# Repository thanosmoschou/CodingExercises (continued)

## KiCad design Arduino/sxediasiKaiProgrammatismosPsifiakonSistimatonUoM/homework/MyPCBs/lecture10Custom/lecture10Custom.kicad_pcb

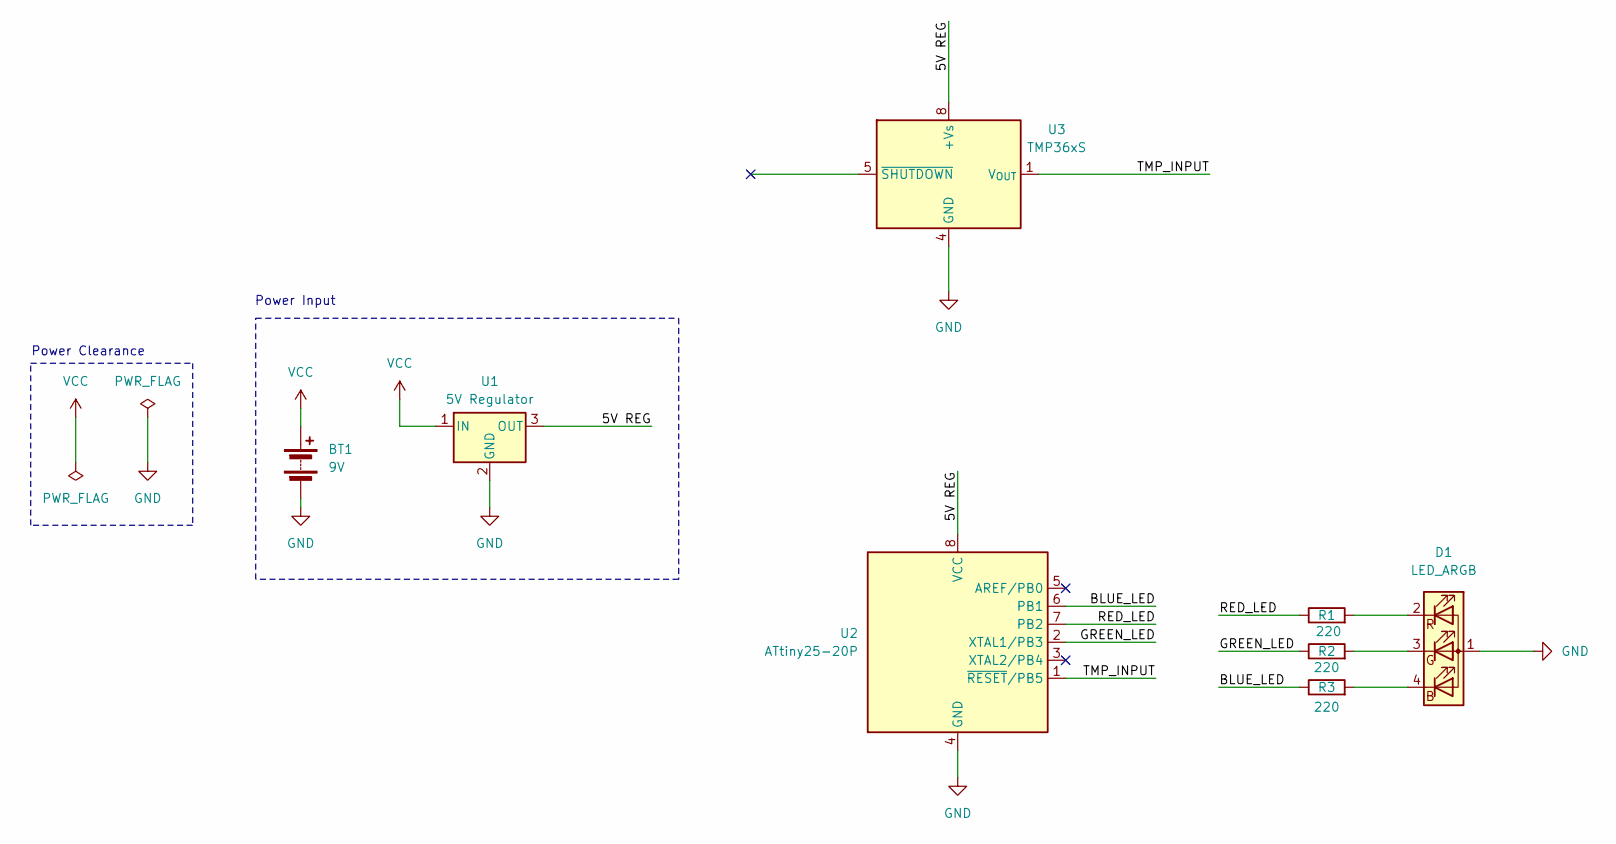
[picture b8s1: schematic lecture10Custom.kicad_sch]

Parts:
BT1: 9V; BatteryHolder_MPD_BA9VPC_1xPP3
D1: LED_ARGB; LED_BL-FL7680RGB
R1, R2, R3: 220; R_Axial_DIN0207_L6.3mm_D2.5mm_P10.16mm_Horizontal
U1: 5V Regulator; TO-220-3_Vertical
U2: ATtiny25-20P; DIP-8_W7.62mm
U3: TMP36xS; SOIC-8_3.9x4.9mm_P1.27mm

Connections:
/5V REG: U1.3 (OUT), U2.8 (VCC), U3.8 (+Vs)
/BLUE_LED: R3.1, U2.6 (PB1)
/GREEN_LED: R2.1, U2.2 (XTAL1/PB3)
/RED_LED: R1.1, U2.7 (PB2)
/TMP_INPUT: U2.1 (~RESET/PB5), U3.1 (V_{OUT})
GND: BT1.2 (-), D1.1 (A), U1.2 (GND), U2.4 (GND), U3.4 (GND)
unnamed: D1.4 (BK), R3.2
unnamed: D1.3 (GK), R2.2
unnamed: D1.2 (RK), R1.2
VCC: BT1.1 (+), U1.1 (IN)

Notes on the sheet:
Power Clearance
Power Input

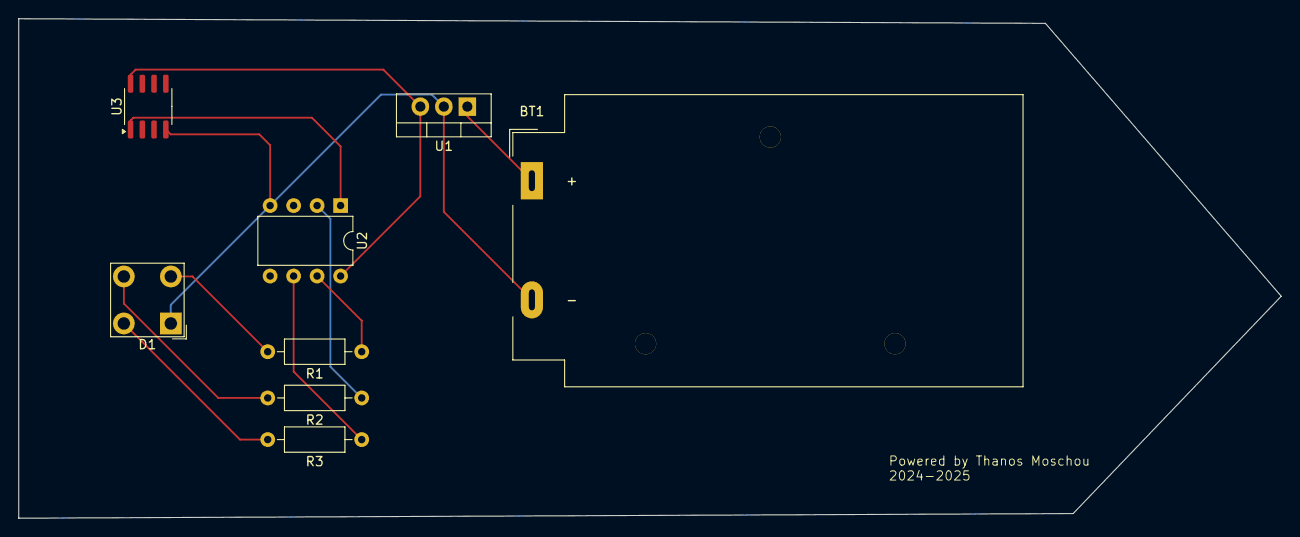
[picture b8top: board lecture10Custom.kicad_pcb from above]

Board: 2 copper layers, 136.5 x 54.0 mm, 8 parts (0 on the bottom side), 10 nets.

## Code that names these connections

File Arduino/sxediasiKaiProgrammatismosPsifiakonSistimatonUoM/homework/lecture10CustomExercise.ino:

/*
Author: Thanos Moschou

Description: A circuit that changes
the LED color depending on temperature.
For temperatures under 0 degrees Celcius
the led color is blue, for temperatures
under 30 degrees Celcius the led is green, 
otherwise it is red.

Components:

1 ATTiny
1 breadboard
1 5V regulator LM7805
1 Temperature Sensor TMP36
1 9V battery
1 RGB Led
3 Resistors 220 Ohm
Jumper wires
*/

int temperPin = A0; // PB5 is also A0
int redPin = 2; // PB2
int bluePin = 1; // PB1
int greenPin = 3; // PB3

void setup()
{
  pinMode(redPin, OUTPUT);
  pinMode(bluePin, OUTPUT);
  pinMode(greenPin, OUTPUT);
  
  digitalWrite(redPin, LOW);
  digitalWrite(bluePin, LOW);
  digitalWrite(greenPin, LOW);
}

void loop()
{
  int d = analogRead(temperPin);
  float temperature = 0.49 * d - 50;
  
  if (temperature < 0) {
    digitalWrite(bluePin, HIGH);
    digitalWrite(redPin, LOW);
    digitalWrite(greenPin, LOW);
  } else if (temperature < 30) {
    digitalWrite(greenPin, HIGH);
    digitalWrite(bluePin, LOW);
    digitalWrite(redPin, LOW);
  } else {
    digitalWrite(redPin, HIGH);
    digitalWrite(bluePin, LOW);
    digitalWrite(greenPin, LOW);
  }
  
  delay(500);
}

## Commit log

2024-06-08 Create LICENSE
2024-06-08 second commit
2024-06-14 add revision android exercise
2024-07-05 add android past exams solutions
2024-07-05 minor changes
2024-07-06 changes to some comments
2024-07-09 mobile development solution september2022
2024-07-16 add july 2024 mobile solution
2024-08-15 add pdc lab solutions
2024-08-16 add lab8
2024-08-16 add lab9
2024-08-17 add lab 10 and lab 11 and made some code format fixes
2024-09-03 modifications
2024-09-09 leetcode changes
2024-09-09 concurrency leetcode problem
2024-09-20 change lab6 of pdc and add Go section
2024-09-21 add exercism exercises
2024-09-22 new exercises
2024-09-23 go exercises
2024-09-23 more go exercises
2024-10-19 complete learning mode in go
2024-10-19 leetcode solution
2024-10-20 more leetcode
2024-10-26 leetcode
2024-10-28 arduino added
2024-10-31 more leetcode75
2024-11-03 arduino practice
2024-11-04 goroutines pdc
2024-11-05 pdc lab3
2024-11-10 arduino exercises
2024-11-11 solidity
2024-11-12 vote
2024-11-12 another solidity example
2024-11-18 add demo for solidity
2024-11-23 more arduino
2024-11-23 minor improvements
2024-12-29 edit
2025-01-29 new revision exercises
2025-01-29 ch4ex3
2025-01-29 new exercises with pcb's
2025-01-29 new custom exerc
2025-01-29 new custom exercise
2025-01-29 edit pcb notes
2025-01-29 notes and new custom exercise
2025-01-29 new custom
2025-01-29 add spring boot section
2025-02-05 edit api
2025-02-07 add spring boot security api exercise
2025-02-11 secure book api v2
2025-02-13 new arduino exercise
2025-02-28 clean structure
2025-03-03 edit spring boot project and create a basic css project of a profile card
2025-03-04 sign up page
2025-03-10 webflux demo
2025-03-10 web flux demo
2025-03-11 video streaming demo
2025-03-20 spring boot demo
2025-03-20 more
2025-05-03 create file uploader with spring boot
2025-05-22 create react exercise
2025-05-31 create a simple rest api exercise with students and courses
2025-06-01 create email sender demo and remove maven notes
